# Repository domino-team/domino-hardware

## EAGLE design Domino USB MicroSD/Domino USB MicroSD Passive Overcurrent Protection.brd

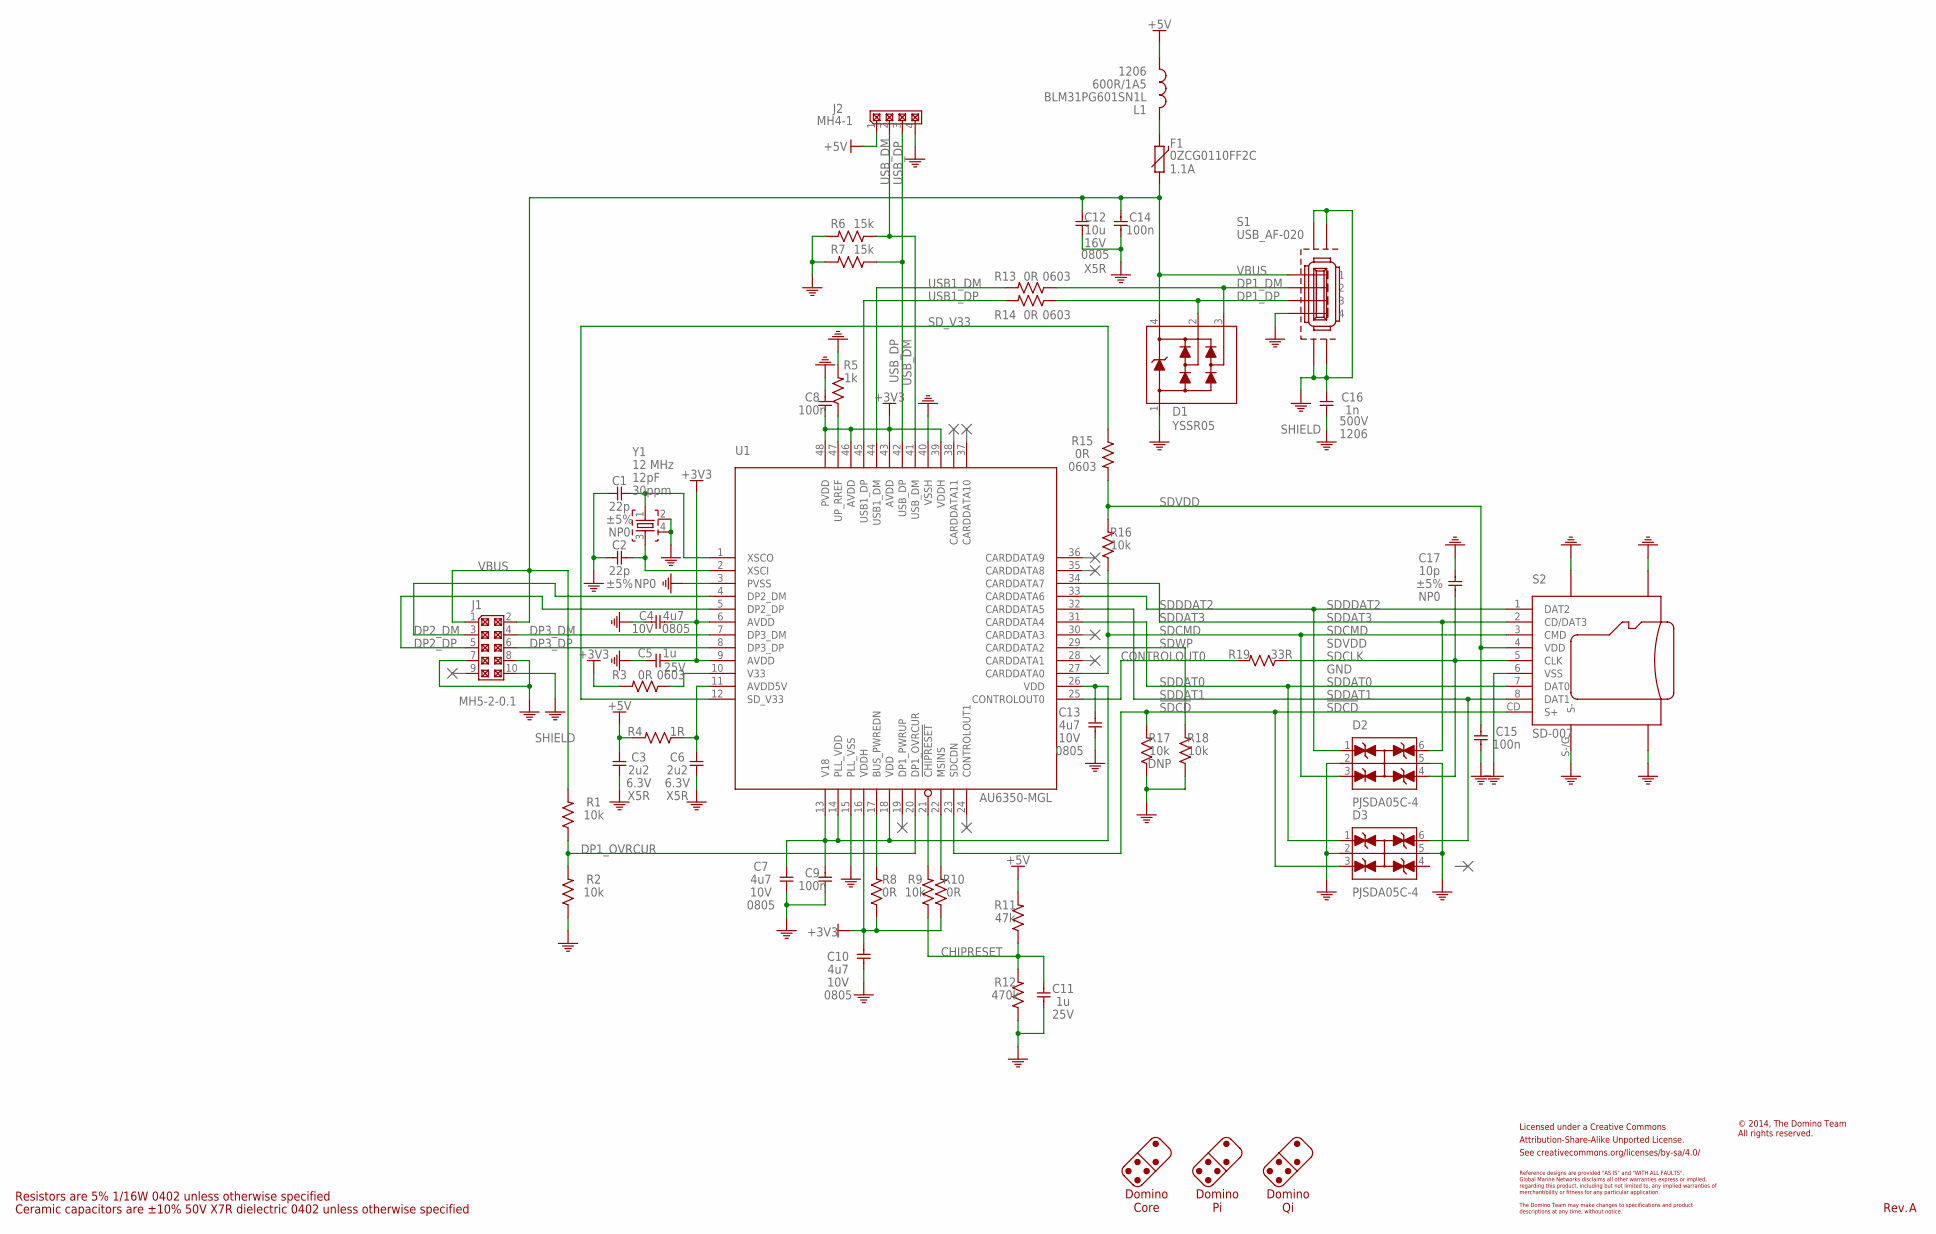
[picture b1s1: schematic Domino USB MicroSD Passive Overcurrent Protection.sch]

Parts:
C1, C2: 22p; C0402; PARTNO C0402_22p_NP0_5%_CER_50V
C3, C6: 2u2; C0402; PARTNO C0402_2u2_X5R_10%_CER_6V3
C4, C7, C10, C13: 4u7; C0805; PARTNO C0805_4u7_X7R_10%_CER_6V3
C5, C11: 1u; C0402; PARTNO C0402_1u_X7R_10%_CER_25V
C8, C9, C14, C15: 100n; C0402; PARTNO C0402_100n_X7R_10%_CER_50V
C12: 10u; C0805; PARTNO C0805_10u_X5R_10%_CER_16V
C16: 1n; C1206; PARTNO C1206_1n_X7R_10%_CER_500V
C17: 10p; C0402; PARTNO C0402_10p_NP0_5%_CER_50V
CC-BY-SA1: CC-BY-SA_LOGO
D1: YSSR05; SOT143B; PARTNO YSSR05
D2, D3: PJSDA05C-4; SOT23-6
F1: 0ZCG0110FF2C; PTC1812; PARTNO 0ZCG0110FF2C
J1: MH5-2-0.1; MH05-2-0.1; PARTNO MH5-2-0.1
J2: MH4-1; MH4-1-0.1; PARTNO MH4-1-0.1
L1: BLM31PG601SN1L; FB1206; PARTNO BLM31PG601SN1L
R1, R2, R9, R16, R17, R18: 10k; R0402; PARTNO R0402_10k_5%_62.5mW
R3, R13, R14, R15: 0R; R0603; PARTNO R0603_0R_5%_125mW
R4: 1R; R0402; PARTNO R0402_1R_5%_62.5mW
R5: 1k; R0402; PARTNO R0402_1k_5%_62.5mW
R6, R7: 15k; R0402; PARTNO R0402_15k_5%_62.5mW
R8, R10: 0R; R0402; PARTNO R0402_0R_5%_62.5mW
R11: 47k; R0402; PARTNO R0402_47k_5%_62.5mW
R12: 470k; R0402; PARTNO R0402_470k_5%_62.5mW
R19: 33R; R0402; PARTNO R0402_33R_5%_62.5mW
S1: USB_AF-020; PARTNO USB_AF-020
S2: SD-007; PARTNO SD-007
U1: AU6350-MGL; LQFP-48_7X7; PARTNO AU6350-MGL
Y1: 12 MHz; CRYSTAL_32X25; PARTNO CRYSTAL_32X25_2SH_12PF_30PPM

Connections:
!CHIPRESET: R9.2, U1.21 (!CHIPRESET)
!SDCD: D3.3, R17.2, S2.CD (S+), U1.23 (SDCDN)
+3V3: C4.2, C5.2, C8.2, C10.2, R3.2, R8.1, R10.1, U1.6 (AVDD), U1.9 (AVDD), U1.16 (VDDH), U1.39 (VDDH), U1.43 (AVDD), U1.46 (AVDD), U1.48 (PVDD)
+5V: C3.1, J2.1, L1.2, R4.2, R11.2
BUS_PWREDN: R8.2, U1.17 (BUS_PWREDN)
CHIPRESET: C11.1, R9.1, R11.1, R12.2
CONTROLOUT0: R19.2, U1.25 (CONTROLOUT0)
DP1_DM: D1.3, R13.1, S1.2
DP1_DP: D1.2, R14.1, S1.3
DP1_OVRCUR: R1.1, R2.2, U1.20 (DP1_OVRCUR)
DP2_DM: J1.3, U1.4 (DP2_DM)
DP2_DP: J1.5, U1.5 (DP2_DP)
DP3_DM: J1.4, U1.7 (DP3_DM)
DP3_DP: J1.6, U1.8 (DP3_DP)
GND: C1.1, C2.1, C3.2, C4.1, C5.1, C6.2, C7.1, C8.1, C9.2, C10.1, C11.2, C12.2, C13.1, C14.2, C15.2, C16.2, C17.2, D1.1, D2.2, D2.5, D3.2, D3.5, J1.7, J1.8, J2.4, R2.1, R5.2, R6.2, R7.2, R12.1, R17.1, R18.1, S1.4, S2.6 (VSS), S2.G$1 (G), S2.G$2 (G), S2.G$3 (G), S2.S-/G (S-), U1.3 (PVSS), U1.15 (PLL_VSS), U1.40 (VSSH), Y1.2, Y1.4
MSINS: R10.2, U1.22 (MSINS)
unnamed: F1.1, L1.1
unnamed: C6.1, R4.1, U1.11 (AVDD5V)
unnamed: R3.1, U1.10 (V33)
SDCLK: C17.1, D2.4, R19.1, S2.5 (CLK)
SDCMD: D2.3, R16.1, S2.3 (CMD), U1.27 (CARDDATA0)
SDDAT0: D3.1, S2.7 (DAT0), U1.31 (CARDDATA4)
SDDAT1: D3.6, S2.8 (DAT1), U1.32 (CARDDATA5)
SDDAT3: D2.6, S2.2 (CD/DAT3), U1.34 (CARDDATA7)
SDDDAT2: D2.1, S2.1 (DAT2), U1.33 (CARDDATA6)
SDVDD: C15.1, R15.2, R16.2, S2.4 (VDD)
SDWP: R18.2, U1.29 (CARDDATA2)
SD_V33: R15.1, U1.12 (SD_V33)
SHIELD: C16.1, J1.10, S1.G$1 (G), S1.G$2 (G), S1.G$3 (G), S1.G$4 (G)
UP_PREF: R5.1, U1.47 (UP_RREF)
USB1_DM: R13.2, U1.44 (USB1_DM)
USB1_DP: R14.2, U1.45 (USB1_DP)
USB_DM: J2.2, R6.1, U1.41 (USB_DM)
USB_DP: J2.3, R7.1, U1.42 (USB_DP)
V18: C7.2, C9.1, C13.2, U1.13 (V18), U1.14 (PLL_VDD), U1.18 (VDD), U1.26 (VDD)
VBUS: C12.1, C14.1, D1.4, F1.2, J1.1, J1.2, R1.2, S1.1
XSCI: C2.2, U1.2 (XSCI), Y1.3
XSCO: C1.2, U1.1 (XSCO), Y1.1

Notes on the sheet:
Ceramic capacitors are ±10% 50V X7R dielectric 0402 unless otherwise specified
Resistors are 5% 1/16W 0402 unless otherwise specified
Licensed under a Creative Commons
Attribution-Share-Alike Unported License.
See creativecommons.org/licenses/by-sa/4.0/
Reference designs are provided "AS IS" and "WITH ALL FAULTS".
regarding this product, including but not limited to, any implied warranties of
The Domino Team may make changes to specifications and product
Global Marine Networks disclaims all other warranties express or implied,
merchantibility or fitness for any particular application.
descriptions at any time, without notice.
Domino Core
Domino Pi
Domino Qi
© 2014, The Domino Team All rights reserved.
Rev.

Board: 2 copper layers, 51 parts (1 on the bottom side), 38 nets, no tracks yet.

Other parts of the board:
DRILEGEND: DRILEGEND
U$3: A5L-LOC
U$4: DOMINO_LOGO_SMALL

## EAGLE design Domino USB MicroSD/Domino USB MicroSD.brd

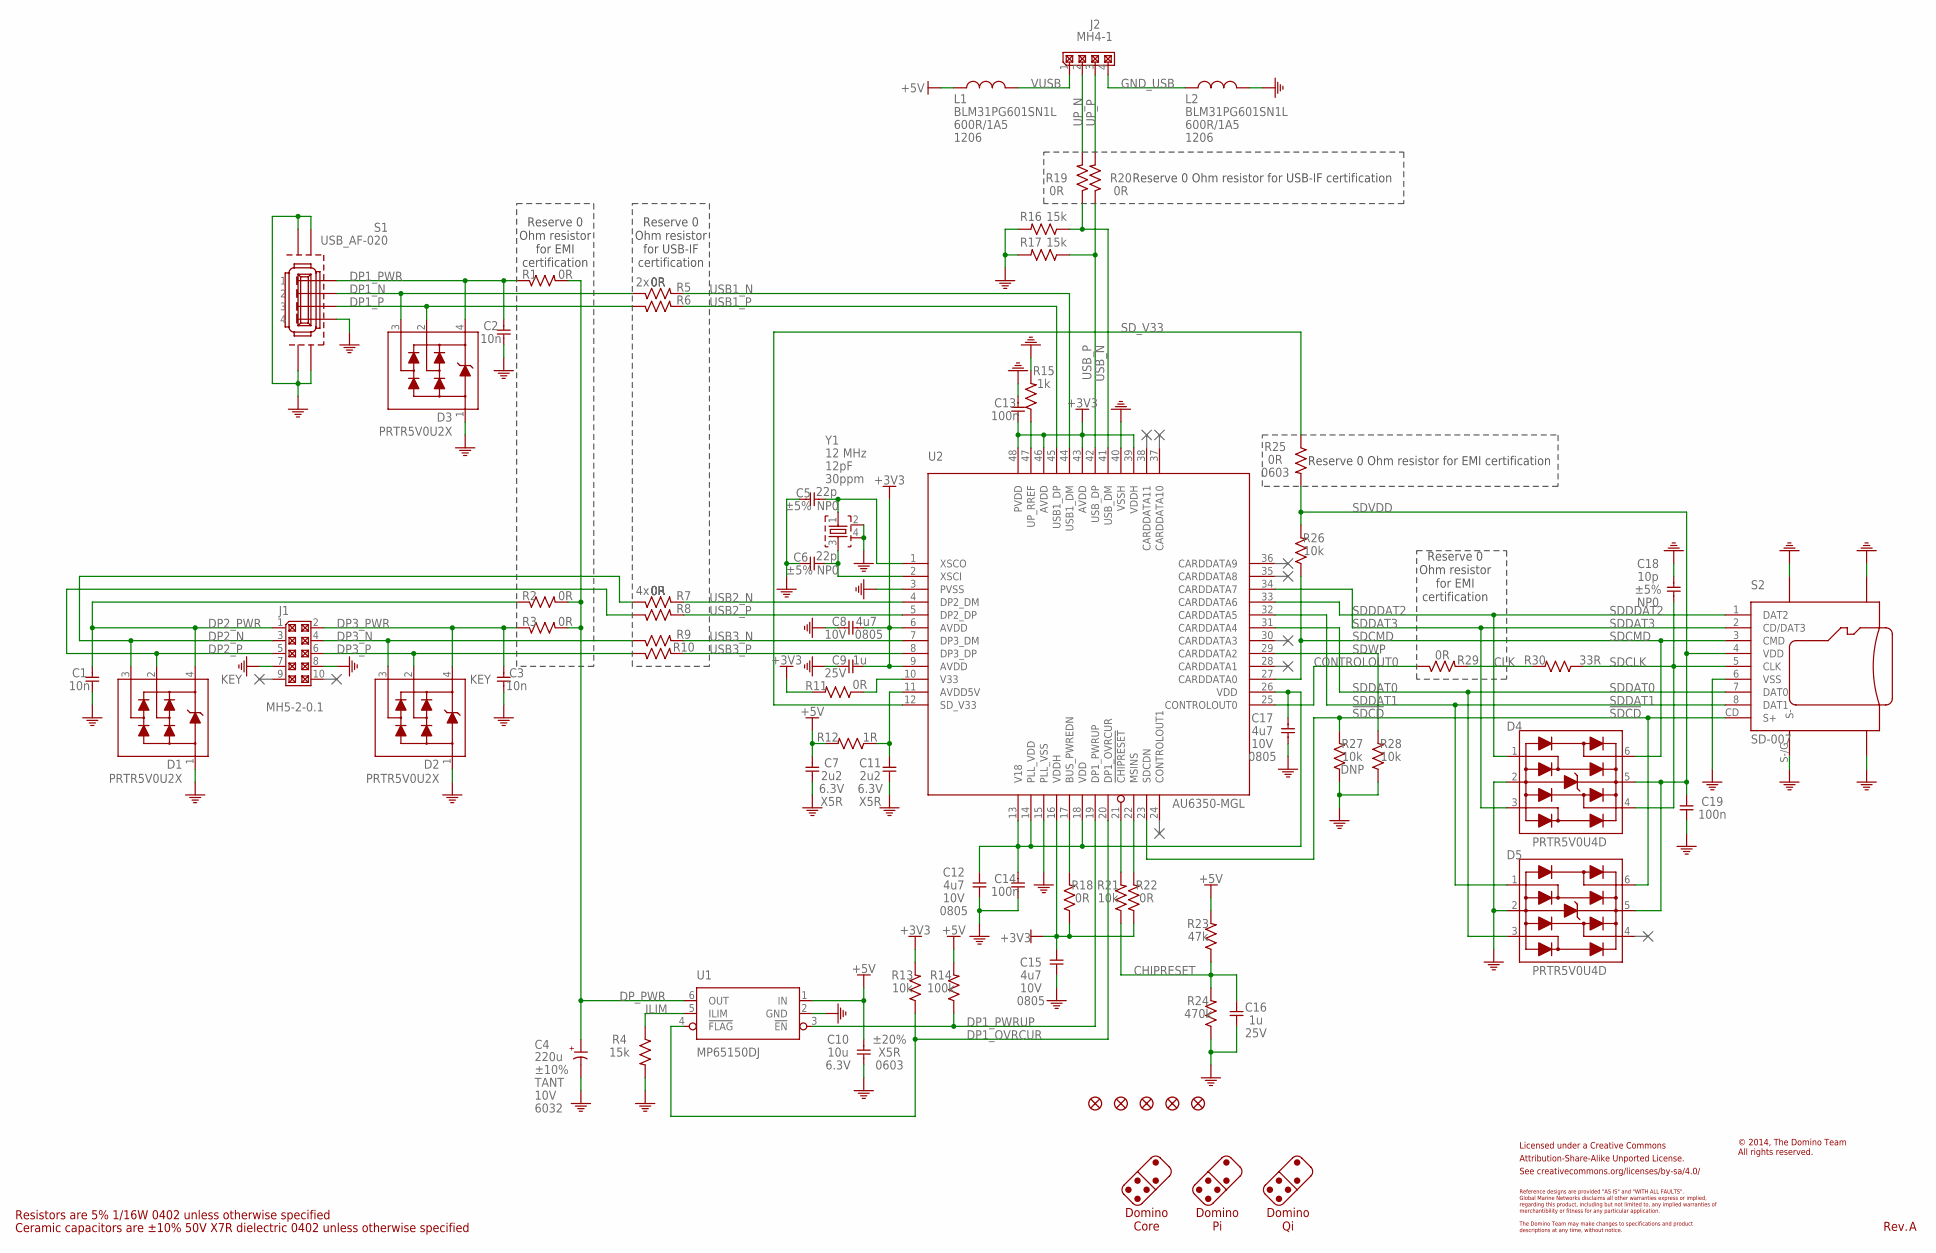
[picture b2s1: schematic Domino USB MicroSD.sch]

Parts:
C1, C2, C3: 10n; C0402; PARTNO C0402_10n_X7R_10%_CER_50V
C4: 220u; C/6032-25; PARTNO CPOLC-6032_220u_20%_TANT_10V
C5, C6: 22p; C0402; PARTNO C0402_22p_NP0_5%_CER_50V
C7, C11: 2u2; C0402; PARTNO C0402_2u2_X5R_10%_CER_6V3
C8, C12, C15, C17: 4u7; C0805; PARTNO C0805_4u7_X7R_10%_CER_6V3
C9, C16: 1u; C0402; PARTNO C0402_1u_X7R_10%_CER_25V
C10: 10u; C0603; PARTNO C0603_10u_X5R_20%_CER_6V3
C13, C14, C19: 100n; C0402; PARTNO C0402_100n_X7R_10%_CER_50V
C18: 10p; C0402; PARTNO C0402_10p_NP0_5%_CER_50V
CC-BY-SA1: CC-BY-SA_LOGO
D1, D2, D3: PRTR5V0U2X; SOT143B; PARTNO PRTR5V0U2X
D4, D5: PRTR5V0U4D; SOT23-6; PARTNO PRTR5V0U4D
F1, F2, F4, F5, F6: FIDUCIAL
J1: MH5-2-0.1; MH05-2-0.1; PARTNO MH5-2-0.1
J2: MH4-1; MH4-1-0.1; PARTNO MH4-1-0.1
L1, L2: BLM31PG601SN1L; FB1206; PARTNO BLM31PG601SN1L
R1, R2, R3, R5, R6, R7, R8, R9, R10, R11, R18, R19, R20, R22, R29: 0R; R0402; PARTNO R0402_0R_5%_62.5mW
R4, R16, R17: 15k; R0402; PARTNO R0402_15k_5%_62.5mW
R12: 1R; R0402; PARTNO R0402_1R_5%_62.5mW
R13, R21, R26, R27, R28: 10k; R0402; PARTNO R0402_10k_5%_62.5mW
R14: 100k; R0402; PARTNO R0402_100k_5%_62.5mW
R15: 1k; R0402; PARTNO R0402_1k_5%_62.5mW
R23: 47k; R0402; PARTNO R0402_47k_5%_62.5mW
R24: 470k; R0402; PARTNO R0402_470k_5%_62.5mW
R25: 0R; R0603; PARTNO R0603_0R_5%_125mW
R30: 33R; R0402; PARTNO R0402_33R_5%_62.5mW
S1: USB_AF-020; PARTNO USB_AF-020
S2: SD-007; PARTNO SD-007
U1: MP65150DJ; SOT23-6; PARTNO MP65150DJ
U2: AU6350-MGL; LQFP-48_7X7; PARTNO AU6350-MGL
Y1: 12 MHz; CRYSTAL_32X25; PARTNO CRYSTAL_32X25_2SH_12PF_30PPM

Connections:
!CHIPRESET: R21.2, U2.21 (!CHIPRESET)
!SDCD: D5.6 (I/O4), R27.2, S2.CD (S+), U2.23 (SDCDN)
+3V3: C8.2, C9.2, C13.2, C15.2, R11.2, R13.2, R18.1, R22.1, U2.6 (AVDD), U2.9 (AVDD), U2.16 (VDDH), U2.39 (VDDH), U2.43 (AVDD), U2.46 (AVDD), U2.48 (PVDD)
+5V: C7.1, C10.1, L1.2, R12.2, R14.2, R23.2, U1.1 (IN)
AVDD5V: C11.1, R12.1, U2.11 (AVDD5V)
BUS_PWREDN: R18.2, U2.17 (BUS_PWREDN)
CHIPRESET: C16.1, R21.1, R23.1, R24.2
CLK: R29.2, R30.2
CONTROLOUT0: R29.1, U2.25 (CONTROLOUT0)
DP1_N: D3.3, R5.1, S1.2
DP1_OVRCUR: R13.1, U1.4 (!FLAG), U2.20 (DP1_OVRCUR)
DP1_P: D3.2, R6.1, S1.3
DP1_PWR: C2.1, D3.4, R1.1, S1.1
DP1_PWRUP: R14.1, U1.3 (!EN), U2.19 (DP1_PWRUP)
DP2_N: D1.3, J1.3, R7.1
DP2_P: D1.2, J1.5, R8.1
DP2_PWR: C1.1, D1.4, J1.1, R2.1
DP3_N: D2.3, J1.4, R9.1
DP3_P: D2.2, J1.6, R10.1
DP3_PWR: C3.1, D2.4, J1.2, R3.1
DP_PWR: C4.1 (+), R1.2, R2.2, R3.2, U1.6 (OUT)
GND: C1.2, C2.2, C3.2, C4.2 (-), C5.1, C6.1, C7.2, C8.1, C9.1, C10.2, C11.2, C12.1, C13.1, C14.2, C15.1, C16.2, C17.1, C18.2, C19.2, D1.1, D2.1, D3.1, D4.2 (GND), D5.2 (GND), J1.7, J1.8, L2.1, R4.2, R15.2, R16.2, R17.2, R24.1, R27.1, R28.1, S1.4, S1.G$1 (G), S1.G$2 (G), S1.G$3 (G), S1.G$4 (G), S2.6 (VSS), S2.G$1 (G), S2.G$2 (G), S2.G$3 (G), S2.S-/G (S-), U1.2 (GND), U2.3 (PVSS), U2.15 (PLL_VSS), U2.40 (VSSH), Y1.2, Y1.4
GND_USB: J2.4, L2.2
ILIM: R4.1, U1.5 (ILIM)
MSINS: R22.2, U2.22 (MSINS)
SDCLK: C18.1, D4.4 (I/O3), R30.1, S2.5 (CLK)
SDCMD: D4.6 (I/O4), R26.1, S2.3 (CMD), U2.27 (CARDDATA0)
SDDAT0: D5.3 (I/O2), S2.7 (DAT0), U2.31 (CARDDATA4)
SDDAT1: D5.1 (I/O1), S2.8 (DAT1), U2.32 (CARDDATA5)
SDDAT3: D4.3 (I/O2), S2.2 (CD/DAT3), U2.34 (CARDDATA7)
SDDDAT2: D4.1 (I/O1), S2.1 (DAT2), U2.33 (CARDDATA6)
SDVDD: C19.1, D4.5 (VCC), D5.5 (VCC), R25.2, R26.2, S2.4 (VDD)
SDWP: R28.2, U2.29 (CARDDATA2)
SD_V33: R25.1, U2.12 (SD_V33)
UP_N: J2.2, R19.2
UP_P: J2.3, R20.2
UP_PREF: R15.1, U2.47 (UP_RREF)
USB1_N: R5.2, U2.44 (USB1_DM)
USB1_P: R6.2, U2.45 (USB1_DP)
USB2_N: R7.2, U2.4 (DP2_DM)
USB2_P: R8.2, U2.5 (DP2_DP)
USB3_N: R9.2, U2.7 (DP3_DM)
USB3_P: R10.2, U2.8 (DP3_DP)
USB_N: R16.1, R19.1, U2.41 (USB_DM)
USB_P: R17.1, R20.1, U2.42 (USB_DP)
V18: C12.2, C14.1, C17.2, U2.13 (V18), U2.14 (PLL_VDD), U2.18 (VDD), U2.26 (VDD)
V33: R11.1, U2.10 (V33)
VUSB: J2.1, L1.1
XSCI: C6.2, U2.2 (XSCI), Y1.3
XSCO: C5.2, U2.1 (XSCO), Y1.1

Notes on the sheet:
Ceramic capacitors are ±10% 50V X7R dielectric 0402 unless otherwise specified
Resistors are 5% 1/16W 0402 unless otherwise specified
Licensed under a Creative Commons
Attribution-Share-Alike Unported License.
See creativecommons.org/licenses/by-sa/4.0/
Reference designs are provided "AS IS" and "WITH ALL FAULTS".
regarding this product, including but not limited to, any implied warranties of
The Domino Team may make changes to specifications and product
Global Marine Networks disclaims all other warranties express or implied,
merchantibility or fitness for any particular application.
descriptions at any time, without notice.
Domino Core
Domino Pi
Domino Qi
© 2014, The Domino Team All rights reserved.
Rev.
KEY
Reserve 0 Ohm resistor for EMI certification
Reserve 0 Ohm resistor for EMI certification
Reserve 0 Ohm resistor for USB-IF certification
Reserve 0 Ohm resistor for USB-IF certification

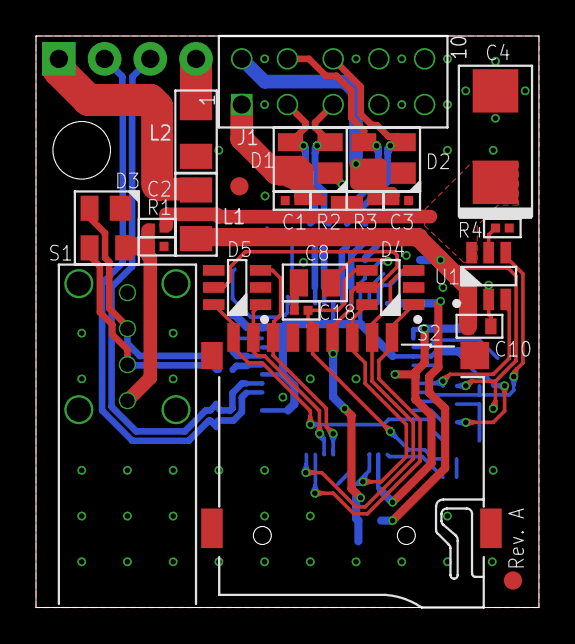
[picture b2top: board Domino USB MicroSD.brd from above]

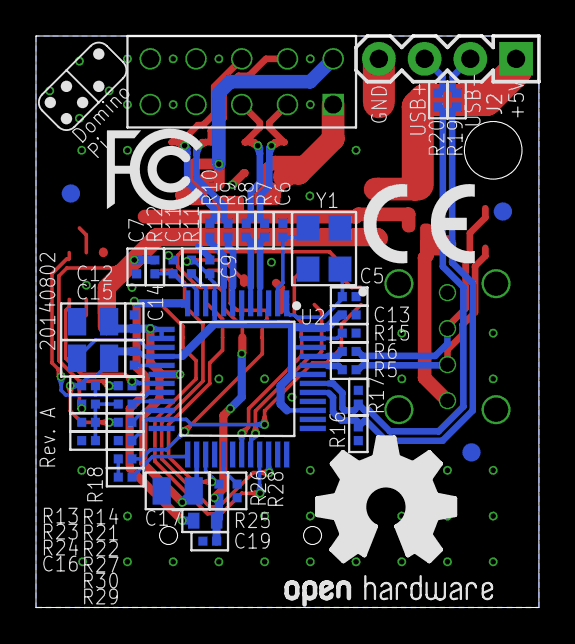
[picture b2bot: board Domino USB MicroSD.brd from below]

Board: 2 copper layers, 27.9 x 31.8 mm, 75 parts (48 on the bottom side), 50 nets.

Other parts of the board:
DRILEGEND: DRILEGEND
U$3: A5L-LOC
U$4: DOMINO_LOGO_SMALL
U$13: CE_LOGO_SMALL
U$15: FCC_LOGO_SMALL
U$16: OPEN_HARDWARE_LOGO

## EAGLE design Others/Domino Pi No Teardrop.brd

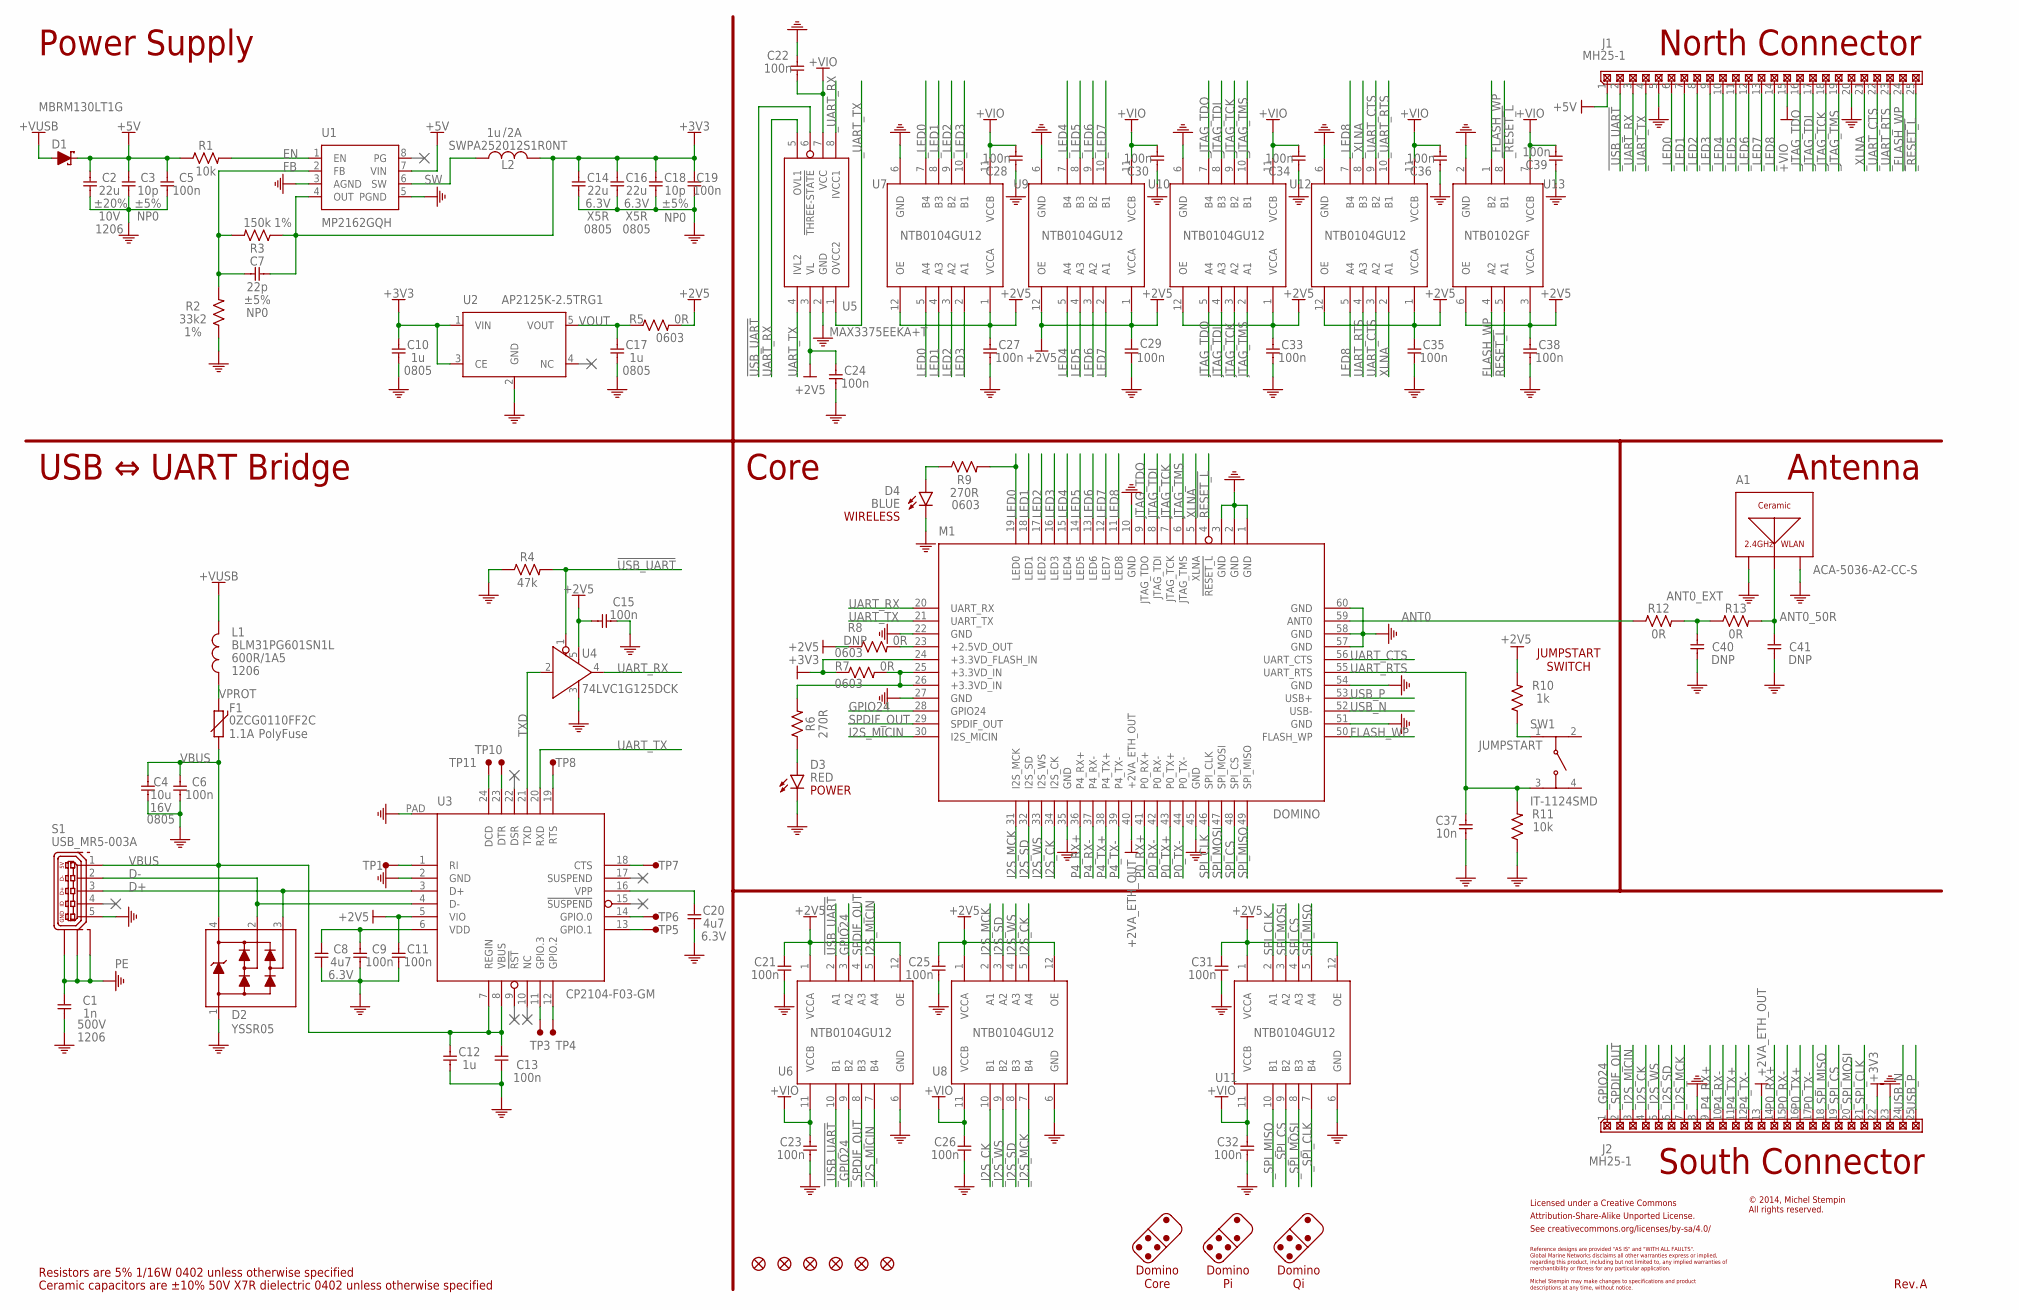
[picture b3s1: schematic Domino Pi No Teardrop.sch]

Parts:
A1: ACA-5036-A2-CC-S
C1: 1n; C1206; PARTNO C1206_1n_X7R_10%_CER_500V
C2: 22u; C1206; PARTNO C1206_22u_X7R_20%_CER_10V
C3, C18: 10p; C0402; PARTNO C0402_10p_NP0_5%_CER_50V
C4: 10u; C0805; PARTNO C0805_10u_X7R_10%_CER_16V
C5, C6, C9, C11, C13, C15, C19, C21, C22, C23, C24, C25, C26, C27, C28, C29, C30, C31, C32, C33, C34, C35, C36, C38, C39: 100n; C0402; PARTNO C0402_100n_X7R_10%_CER_50V
C7: 22p; C0402; PARTNO C0402_22p_NP0_5%_CER_50V
C8, C20: 4u7; C0402; PARTNO C0402_4u7_X7R_10%_CER_6V3
C10, C17: 1u; C0805; PARTNO C0805_1u_X7R_10%_CER_50V
C12: 1u; C0402; PARTNO C0402_1u_X7R_10%_CER_50V
C14, C16: 22u; C0805; PARTNO C0805_22u_X5R_20%_CER_6V3
C37: 10n; C0402; PARTNO C0402_10n_X7R_10%_CER_50V
C40, C41: DNP; C0402; PARTNO C0402_DNP
CC-BY-SA: CC-BY-SA_LOGO
D1: MBRM130LT1G; DO-216AA; PARTNO MBRM130LT1G
D2: YSSR05; SOT143B; PARTNO YSSR05
D3: RED; LED0603; PARTNO LED0603-RED
D4: BLUE; LED0603; PARTNO LED0603-BLUE
F1: 0ZCG0110FF2C; PTC1812; PARTNO 0ZCG0110FF2C
F2, F3, F4, F5, F6, F7: FIDUCIAL
J1, J2: MH25-1; MH25-1-0.1; PARTNO MH25-1-0.1
L1: BLM31PG601SN1L; FB1206; PARTNO BLM31PG601SN1L
L2: SWPA252012S1R0NT; SWPA252012S; PARTNO SWPA252012SMT
M1: DOMINO; PARTNO DOMINO-CORE
R1, R11: 10k; R0402; PARTNO R0402_10k_5%_62.5mW
R2: 33k2; R0402; PARTNO R0402_33k2_1%_62.5mW
R3: 150k; R0402; PARTNO R0402_150k_1%_62.5mW
R4: 47k; R0402; PARTNO R0402_47k_5%_62.5mW
R5, R7, R8: 0R; R0603; PARTNO R0603_0R_5%_125mW
R6: 270R; R0402; PARTNO R0603_270R_5%_125mW
R9: 270R; R0603; PARTNO R0603_270R_5%_125mW
R10: 1k; R0402; PARTNO R0402_1k_5%_62.5mW
R12, R13: 0R; R0402; PARTNO R0402_0R_5%_62.5mW
S1: USB_MR5-003A; PARTNO USB MR5-003A
SW1: IT-1124SMD; PARTNO IT-1124SMD
TP1, TP3, TP4, TP5, TP6, TP7, TP8, TP10, TP11: TEST_PAD
U1: MP2162GQH; QFN-8_2X1.5; PARTNO MP2162GQH
U2: AP2125K-2.5TRG1; SOT23-5
U3: CP2104-F03-GM; QFN-25_4X4; PARTNO CP2104-F03-GM
U4: 74LVC1G125DCK; SC70; PARTNO 74LVC1G125DCK
U5: MAX3375EEKA+T; SOT23-8; PARTNO MAX3375EEKA+T
U6, U7, U8, U9, U10, U11, U12: NTB0104GU12; XQFN-12; PARTNO NTB0104GU12
U13: NTB0102GF; SOT1089; PARTNO NTB0102GF

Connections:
!RESET_L: M1.4 (!RESET_L), U13.5 (A1)
!USB_UART: R4.2, U4.1 (!OE), U5.6 (!THREE-STATE), U6.2 (A1)
!_RESET_L: J1.25, U13.8 (B1)
!_USB_UART: J1.2, U6.10 (B1)
+2.5VD_OUT: M1.23 (+2.5VD_OUT), R8.2
+2V5: C11.1, C15.2, C21.1, C24.2, C25.1, C27.2, C29.2, C31.1, C33.2, C35.2, C38.2, R5.2, R8.1, R10.2, U3.5 (VIO), U4.5 (VCC), U5.3 (VL), U6.1 (VCCA), U6.12 (OE), U7.1 (VCCA), U7.12 (OE), U8.1 (VCCA), U8.12 (OE), U9.1 (VCCA), U9.12 (OE), U10.1 (VCCA), U10.12 (OE), U11.1 (VCCA), U11.12 (OE), U12.1 (VCCA), U12.12 (OE), U13.3 (VCCA), U13.6 (OE)
+2VA_ETH_OUT: J2.13, M1.40 (+2VA_ETH_OUT)
+3.3VD_IN: M1.25 (+3.3VD_IN), M1.26 (+3.3VD_IN), R6.2, R7.2
+3V3: C7.2, C10.1, C14.1, C16.1, C18.1, C19.1, J2.22, L2.2, M1.24 (+3.3VD_FLASH_IN), R3.1, R7.1, U1.4 (OUT), U2.1 (VIN), U2.3 (CE)
+5V: C2.1, C3.1, C5.1, D1.1 (C), J1.1, R1.1, U1.7 (VIN)
+VIO: C22.1, C23.1, C26.1, C28.1, C30.1, C32.1, C34.1, C36.1, C39.1, J1.15, U5.7 (VCC), U6.11 (VCCB), U7.11 (VCCB), U8.11 (VCCB), U9.11 (VCCB), U10.11 (VCCB), U11.11 (VCCB), U12.11 (VCCB), U13.7 (VCCB)
+VUSB: D1.2 (A), L1.1
ANT0: M1.59 (ANT0), R12.1
ANT0_50R: A1.FEED (A), C41.1, R13.2
ANT0_EXT: C40.1, R12.2, R13.1
BLUE_LED: D4.2 (A), R9.1
D+: D2.3, S1.3, U3.3 (D+)
D-: D2.2, S1.2, U3.4 (D-)
EN: R1.2, U1.1 (EN)
FB: C7.1, R2.2, R3.2, U1.2 (FB)
FLASH_WP: M1.50 (FLASH_WP), U13.4 (A2)
GND: A1.GND$1 (GND), A1.GND$2 (GND), C1.2, C2.2, C3.2, C4.2, C5.2, C6.2, C8.2, C9.2, C10.2, C11.2, C12.2, C13.2, C14.2, C15.1, C16.2, C17.2, C18.2, C19.2, C20.2, C21.2, C22.2, C23.2, C24.1, C25.2, C26.2, C27.1, C28.2, C29.1, C30.2, C31.2, C32.2, C33.1, C34.2, C35.1, C36.2, C37.2, C38.1, C39.2, C40.2, C41.2, D2.1, D3.1 (C), D4.1 (C), J1.5, J1.20, J2.8, J2.23, M1.1 (GND), M1.2 (GND), M1.3 (GND), M1.10 (GND), M1.22 (GND), M1.27 (GND), M1.35 (GND), M1.45 (GND), M1.51 (GND), M1.54 (GND), M1.57 (GND), M1.58 (GND), M1.60 (GND), R2.1, R4.1, R11.1, S1.5, U1.3 (AGND), U1.5 (PGND), U2.2 (GND), U3.2 (GND), U3.PAD, U4.3 (GND), U5.2 (GND), U6.6 (GND), U7.6 (GND), U8.6 (GND), U9.6 (GND), U10.6 (GND), U11.6 (GND), U12.6 (GND), U13.2 (GND)
GPIO24: M1.28 (GPIO24), U6.3 (A2)
I2S_CK: M1.34 (I2S_CK), U8.5 (A4)
I2S_MCK: M1.31 (I2S_MCK), U8.2 (A1)
I2S_MICIN: M1.30 (I2S_MICIN), U6.5 (A4)
I2S_SD: M1.32 (I2S_SD), U8.3 (A2)
I2S_WS: M1.33 (I2S_WS), U8.4 (A3)
JTAG_TCK: M1.7 (JTAG_TCK), U10.3 (A2)
JTAG_TDI: M1.8 (JTAG_TDI), U10.4 (A3)
JTAG_TDO: M1.9 (JTAG_TDO), U10.5 (A4)
JTAG_TMS: M1.6 (JTAG_TMS), U10.2 (A1)
JUMPSTART: R10.1, SW1.1
LED0: M1.19 (LED0), R9.2, U7.5 (A4)
LED1: M1.18 (LED1), U7.4 (A3)
LED2: M1.17 (LED2), U7.3 (A2)
LED3: M1.16 (LED3), U7.2 (A1)
LED4: M1.15 (LED4), U9.5 (A4)
LED5: M1.14 (LED5), U9.4 (A3)
LED6: M1.13 (LED6), U9.3 (A2)
LED7: M1.12 (LED7), U9.2 (A1)
LED8: M1.11 (LED8), U12.5 (A4)
unnamed: D3.2 (A), R6.1
unnamed: TP1.1, U3.1 (RI)
unnamed: TP3.1, U3.11 (GPIO.3)
unnamed: TP4.1, U3.12 (GPIO.2)
unnamed: TP7.1, U3.18 (CTS)
unnamed: TP10.1, U3.23 (DTR)
unnamed: TP11.1, U3.24 (DCD)
unnamed: TP8.1, U3.19 (RTS)
unnamed: TP6.1, U3.14 (GPIO.0)
unnamed: TP5.1, U3.13 (GPIO.1)
unnamed: C20.1, U3.16 (VPP)
P0_RX+: J2.14, M1.41 (P0_RX+)
P0_RX-: J2.15, M1.42 (P0_RX-)
P0_TX+: J2.16, M1.43 (P0_TX+)
P0_TX-: J2.17, M1.44 (P0_TX-)
P4_RX+: J2.9, M1.36 (P4_RX+)
P4_RX-: J2.10, M1.37 (P4_RX-)
P4_TX+: J2.11, M1.38 (P4_TX+)
P4_TX-: J2.12, M1.39 (P4_TX-)
PE: C1.1, S1.S$1 (M0), S1.S$2 (M1), S1.S$3 (M2)
SPDIF_OUT: M1.29 (SPDIF_OUT), U6.4 (A3)
SPI_CLK: M1.46 (SPI_CLK), U11.2 (A1)
SPI_CS: M1.48 (SPI_CS), U11.4 (A3)
SPI_MISO: M1.49 (SPI_MISO), U11.5 (A4)
SPI_MOSI: M1.47 (SPI_MOSI), U11.3 (A2)
SW: L2.1, U1.6 (SW)
TXD: U3.21 (TXD), U4.2 (A)
UART_CTS: M1.56 (UART_CTS), U12.3 (A2)
UART_RTS: C37.1, M1.55 (UART_RTS), R11.2, SW1.3, U12.4 (A3)
UART_RX: M1.20 (UART_RX), U4.4 (Y), U5.5 (OVL1)
UART_TX: M1.21 (UART_TX), U3.20 (RXD), U5.4 (IVL2)
USB_N: J2.24, M1.52 (USB-)
USB_P: J2.25, M1.53 (USB+)
VBUS: C4.1, C6.1, C12.1, C13.1, D2.4, F1.2, S1.1, U3.7 (REGIN), U3.8 (VBUS)
VDD: C8.1, C9.1, U3.6 (VDD)
VOUT: C17.1, R5.1, U2.5 (VOUT)
VPROT: F1.1, L1.2
XLNA: M1.5 (XLNA), U12.2 (A1)
_FLASH_WP: J1.24, U13.1 (B2)
_GPIO24: J2.1, U6.9 (B2)
_I2S_CK: J2.4, U8.10 (B1)
_I2S_MCK: J2.7, U8.7 (B4)
_I2S_MICIN: J2.3, U6.7 (B4)
_I2S_SD: J2.6, U8.8 (B3)
_I2S_WS: J2.5, U8.9 (B2)
_JTAG_TCK: J1.18, U10.9 (B2)
_JTAG_TDI: J1.17, U10.8 (B3)
_JTAG_TDO: J1.16, U10.7 (B4)
_JTAG_TMS: J1.19, U10.10 (B1)
_LED0: J1.6, U7.7 (B4)
_LED1: J1.7, U7.8 (B3)
_LED2: J1.8, U7.9 (B2)
_LED3: J1.9, U7.10 (B1)
_LED4: J1.10, U9.7 (B4)
_LED5: J1.11, U9.8 (B3)
_LED6: J1.12, U9.9 (B2)
_LED7: J1.13, U9.10 (B1)
_LED8: J1.14, U12.7 (B4)
_SPDIF_OUT: J2.2, U6.8 (B3)
_SPI_CLK: J2.21, U11.7 (B4)
_SPI_CS: J2.19, U11.9 (B2)
_SPI_MISO: J2.18, U11.10 (B1)
_SPI_MOSI: J2.20, U11.8 (B3)
_UART_CTS: J1.22, U12.9 (B2)
_UART_RTS: J1.23, U12.10 (B1)
_UART_RX: J1.3, U5.8 (IVCC1)
_UART_TX: J1.4, U5.1 (OVCC2)
_XLNA: J1.21, U12.8 (B3)

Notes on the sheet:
PolyFuse
Power Supply
North Connector
South Connector
Antenna
Core
USB ⇔ UART Bridge
Ceramic capacitors are ±10% 50V X7R dielectric 0402 unless otherwise specified
Resistors are 5% 1/16W 0402 unless otherwise specified
Licensed under a Creative Commons
Attribution-Share-Alike Unported License.
See creativecommons.org/licenses/by-sa/4.0/
Reference designs are provided "AS IS" and "WITH ALL FAULTS".
regarding this product, including but not limited to, any implied warranties of
Michel Stempin may make changes to specifications and product
Global Marine Networks disclaims all other warranties express or implied,
merchantibility or fitness for any particular application.
descriptions at any time, without notice.
© 2014, Michel Stempin All rights reserved.
Rev.
Domino Core
Domino Pi
Domino Qi
WIRELESS
POWER
JUMPSTART SWITCH

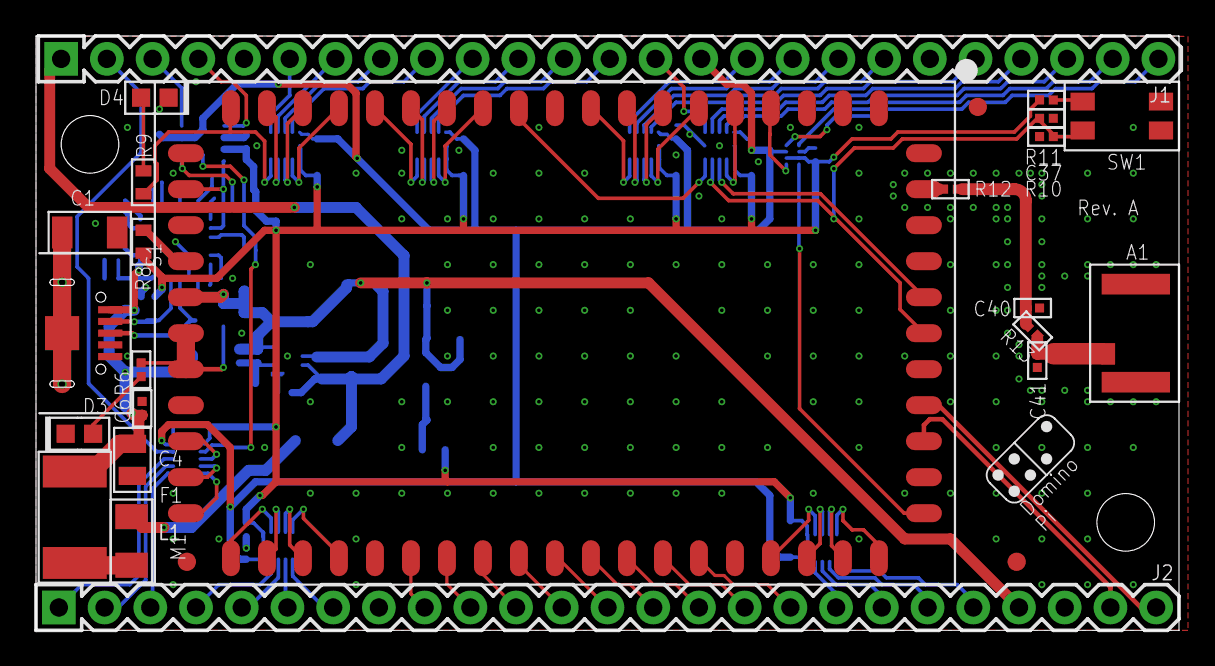
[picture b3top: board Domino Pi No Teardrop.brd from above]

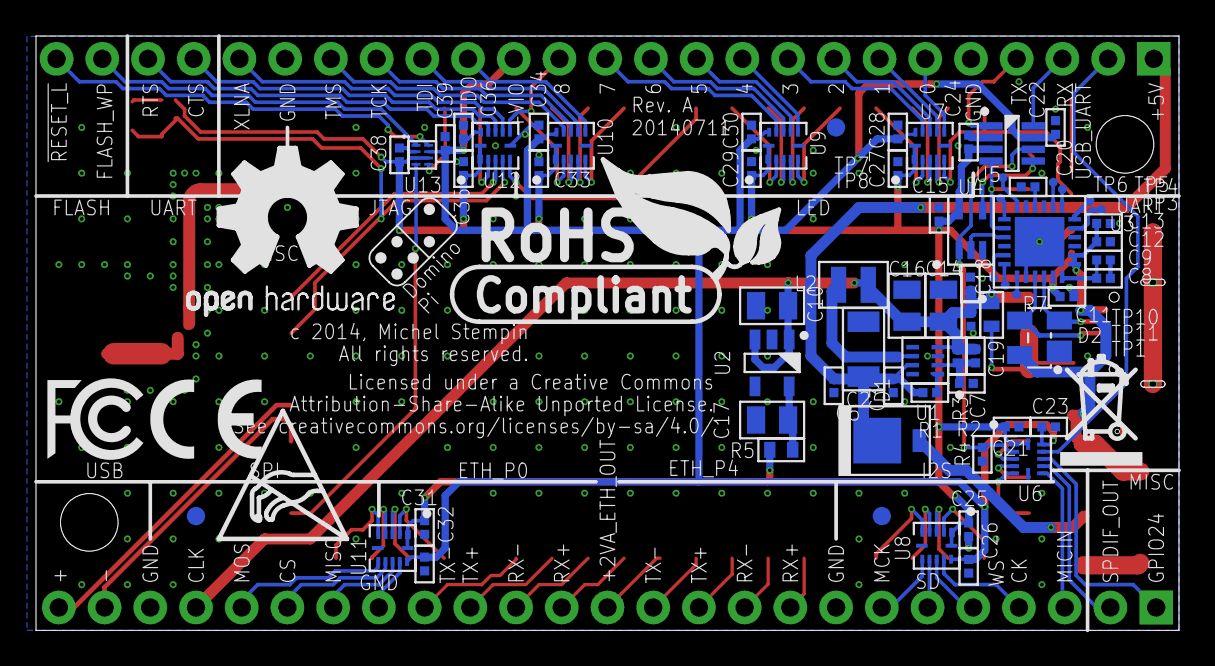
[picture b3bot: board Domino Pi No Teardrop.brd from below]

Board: 2 copper layers, 63.5 x 33.0 mm, 106 parts (76 on the bottom side), 110 nets.

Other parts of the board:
DRILEGEND: DRILEGEND
U$7, U$9: DOMINO_LOGO_SMALL
U$28: A5L-LOC
U$36: ESD_LOGO
U$38: OPEN_HARDWARE_LOGO
U$39: RECYCLE_BIN_LOGO
U$40: ROHS_LOGO
U$41: CE_LOGO_SMALL
U$42: FCC_LOGO_SMALL

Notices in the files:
parts and their libraries:
Domino: See creativecommons.org/licenses/by-sa/4.0/ for details.
Domino: See creativecommons.org/licenses/by-sa/3.0/ for details.
Domino: Copyright © 2012, Michel Stempin, All rights reserved
Licenced under Creative Commons CC BY-SA 3.0 license.
